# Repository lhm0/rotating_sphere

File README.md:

# Rotating LED Sphere – RP2040 POV Display
**UPDATE December 24th, 2025**
I have made a change to the header of the motor in order to make the connection to the sphere stronger and long term stable.

However, alignment of the rotor now is done by placing washers between header and pcb, if necessary.

Furthermore, I have added a file "print_instructions.pdf" in the /mechanics subfolder, with slicer images of the parts that need nut inlays.

**UPDATE August 29th, 2025**
There are two push switches on the power supply pcb, that control the speed of the motor. The "speed" button is used to increase the motor speed step by step. Once the maximum speed is reached, it jumps back to zero. The "off" button turns the motor off.

However, The buttons were previously positioned at the same height as the power supply circuit board, very close to the rotating sphere assembly. To reduce the risk of injury, I have moved the buttons to the center of the power supply housing in the latest version of the housing. The movement of the two buttons is transferred to the switches on the circuit board purely mechanically, so that no modification of the circuit board is necessary.

**UPDATE May 29th, 2025**

In the meantime I had the new power supply board built and could test it the last couple of days. **It works fine as expected.** 

Power is now supplied from a **standard USB-C power supply** with power delivery ("PD") function via an off-the-shelf USB-C cable. I am using the Apple power supply of my MacBook. The CH224k for controlling the voltage setting works extremely well. The voltage can be set with a 3 bit dip switch, easily. When set to 15 V, the transmitted energy to the LED board is sufficient even for the highest brightness setting. Of course, the losses of the wireless power transmission show up as heat, but the temperature looks reasonable to me.

The motor power supply has a **stronger step-down converter chip** now (TPS54302 instead of TPS54202 in the old design). The circuit allows for up to 3A of motor current. Furthermore, I introduced a button control logic for setting the motor speed in 5 steps. There are two buttons: increase speed, and OFF. This eliminates the potentiometer and the on/off switch in the old design.

Finally, I **increased the diameter of the circular hole in the middle of the pcb**, which allows for a significantly larger and stronger motor to LED-board connection. The tray disk has a larger diameter now. The 4 holes in the secondary coil pcb are now being used for securing the LED assembly to the motor.

In order to fit the new pcb, I had to modify the housing. Please find the related files in this repository.

**UPDATE May 10th, 2025**
I am currently working on an update of the power supply. The idea is to replace the 12V power plug with an USB-C PD (power delivery) power supply. I am interested in the CH224K, which manages the voltage negotiation with the USB PD. This would allow us to use a standard USB-C charger (probably about 25 - 35 W) for supplying the device. USB power delivery can provide 5, 9, 12, 15, or 20V. This is exactly the range needed for the rotating sphere. At the same time I will replace the motor power regulator with a stronger one. Currently, the motor current cannot go above 2A, which is just barely sufficient.

If you are interested, stay tuned. However, it will definitely take 4 weeks, probably more, to get it done.

**UPDATE April 30th, 2025**
@randybeever5206 made me aware (**thank you!**), that the value of R403, R404, and R405 on the main display board should be 270 Ohm according to the schematic, but the properties field and the corresponding line in the production file refers to a 1k resistor instead. Let me explain:

1. these three resistors set the forward peak current of the LEDs. 1k corresponds to 20 mA, 270 Ohms corresponds to 75 mA. 
2. I had copied this part of the schematic from an earlier project, changed the value but missed to change the component in the production data. As a result, I worked with 20mA, although I thought it was 75.
3. I have changed the resistors in my unit from 1k to 270 Ohm in the meantime (what a pain: these are 0402 resistors!). Yes, it is significantly brighter. For some reason, colors look even more saturated, now. The color animation, which can be seen in the video, looks stunning.
4. However, higher brightness means higher power consumption. If you supply the device with a 12 V power plug (12V, 2A), you can not run it at 100% brightness. I found that the processor crashes, when you go too high. This is obviously a voltage breakdown.
5. Fortunately, I designed the power supply such that it can be operated with up to 24V. When you run the sphere with 17V or above, you can go up to 100% brightness.
6. Here is my recommendation: use 270 Ohm resistors. If you run the device at 12V, you need to reduce the brightness setting, so that the device works flawlessly. If you want more, you need a power supply with more than 17V, 2 or better 3 A (consumption depends on motor speed).
7. I have updated the schematic and the production file in the meantime.

## 📌 Project Overview

This project describes the design and construction of a **rotating LED sphere** using the **persistence-of-vision (POV)** principle.  
The device is controlled by a **Raspberry Pi RP2040 microcontroller** and is capable of displaying **videos, animated GIFs**, and **static images** on a spherical 3D surface.

The project is inspired by the Las Vegas Sphere – scaled down to desktop size, but packed with smart engineering like **wireless power transmission**, **real-time SDIO video streaming**, and **web-based remote control**.

All hardware, software, PCB layouts and 3D printable parts are **open source** and included in this repository.

---

## ✨ Features

- 🟡 64 RGB LEDs arranged to form a 170 mm spherical POV display  
- 📊 Display resolution: **64 × 256 pixels** **(corrected: it is NOT 128 x 256)**  
- 🎞️ Supports **.rs64** video/image format (GIFs, animations, stills)  
- 💾 Real-time video streaming from **SD card via SDIO (4-bit)**  
- ⚙️ Driven by an **RP2040** using fast **PIO-based multiplexing**  
- 🌐 Optional **ESP01s** module creates a web-based control interface  
- 🔌 **Wireless power** using a Royer converter – no slip rings needed  
- 🧠 Designed to be **easy to build**, with a minimal part count  
- 🧰 All files included: **KiCad PCB**, **PlatformIO code**, **3D models**

---

## 🧱 System Components

- **RP2040 microcontroller** (via Raspberry Pi Pico or custom PCB)  
- **ESP01s (optional)** for Wi-Fi control and web interface  
- **SD card slot** (with high-speed SDIO interface)  
- **24-bit shift register** and **MOSFETs** for LED driving  
- **3D-printed mechanical components** (rotor, housing, mounts)  
- **Wireless power transmission** with printed transmitter/receiver coils  
- **Hall sensor** for rotation angle synchronization  
- **Custom `.rs64` video format** with 8 brightness levels via PWM

---

## 🛠️ How to Build

The build process is documented in a [step-by-step video tutorial](https://www.youtube.com/yourvideolink), covering:

1. Mechanical design & 3D printing  
2. Rotor balancing and alignment  
3. Soldering the LED matrix  
4. Power & wireless energy transmission  
5. Programming the RP2040 and ESP01s  
6. Creating `.rs64` files from GIFs and videos  
7. Using the web interface

For detailed instructions, see the [`docs/`](./docs) folder.

---

## 📜 License

This project is licensed under the **Creative Commons BY-NC-SA 4.0** license.  
You are free to **use, adapt, and share** this work for **non-commercial** purposes,  
as long as you give proper credit and share your work under the same terms.

> ✏️ Especially welcomed: use in education, maker communities, and open-source development!

---

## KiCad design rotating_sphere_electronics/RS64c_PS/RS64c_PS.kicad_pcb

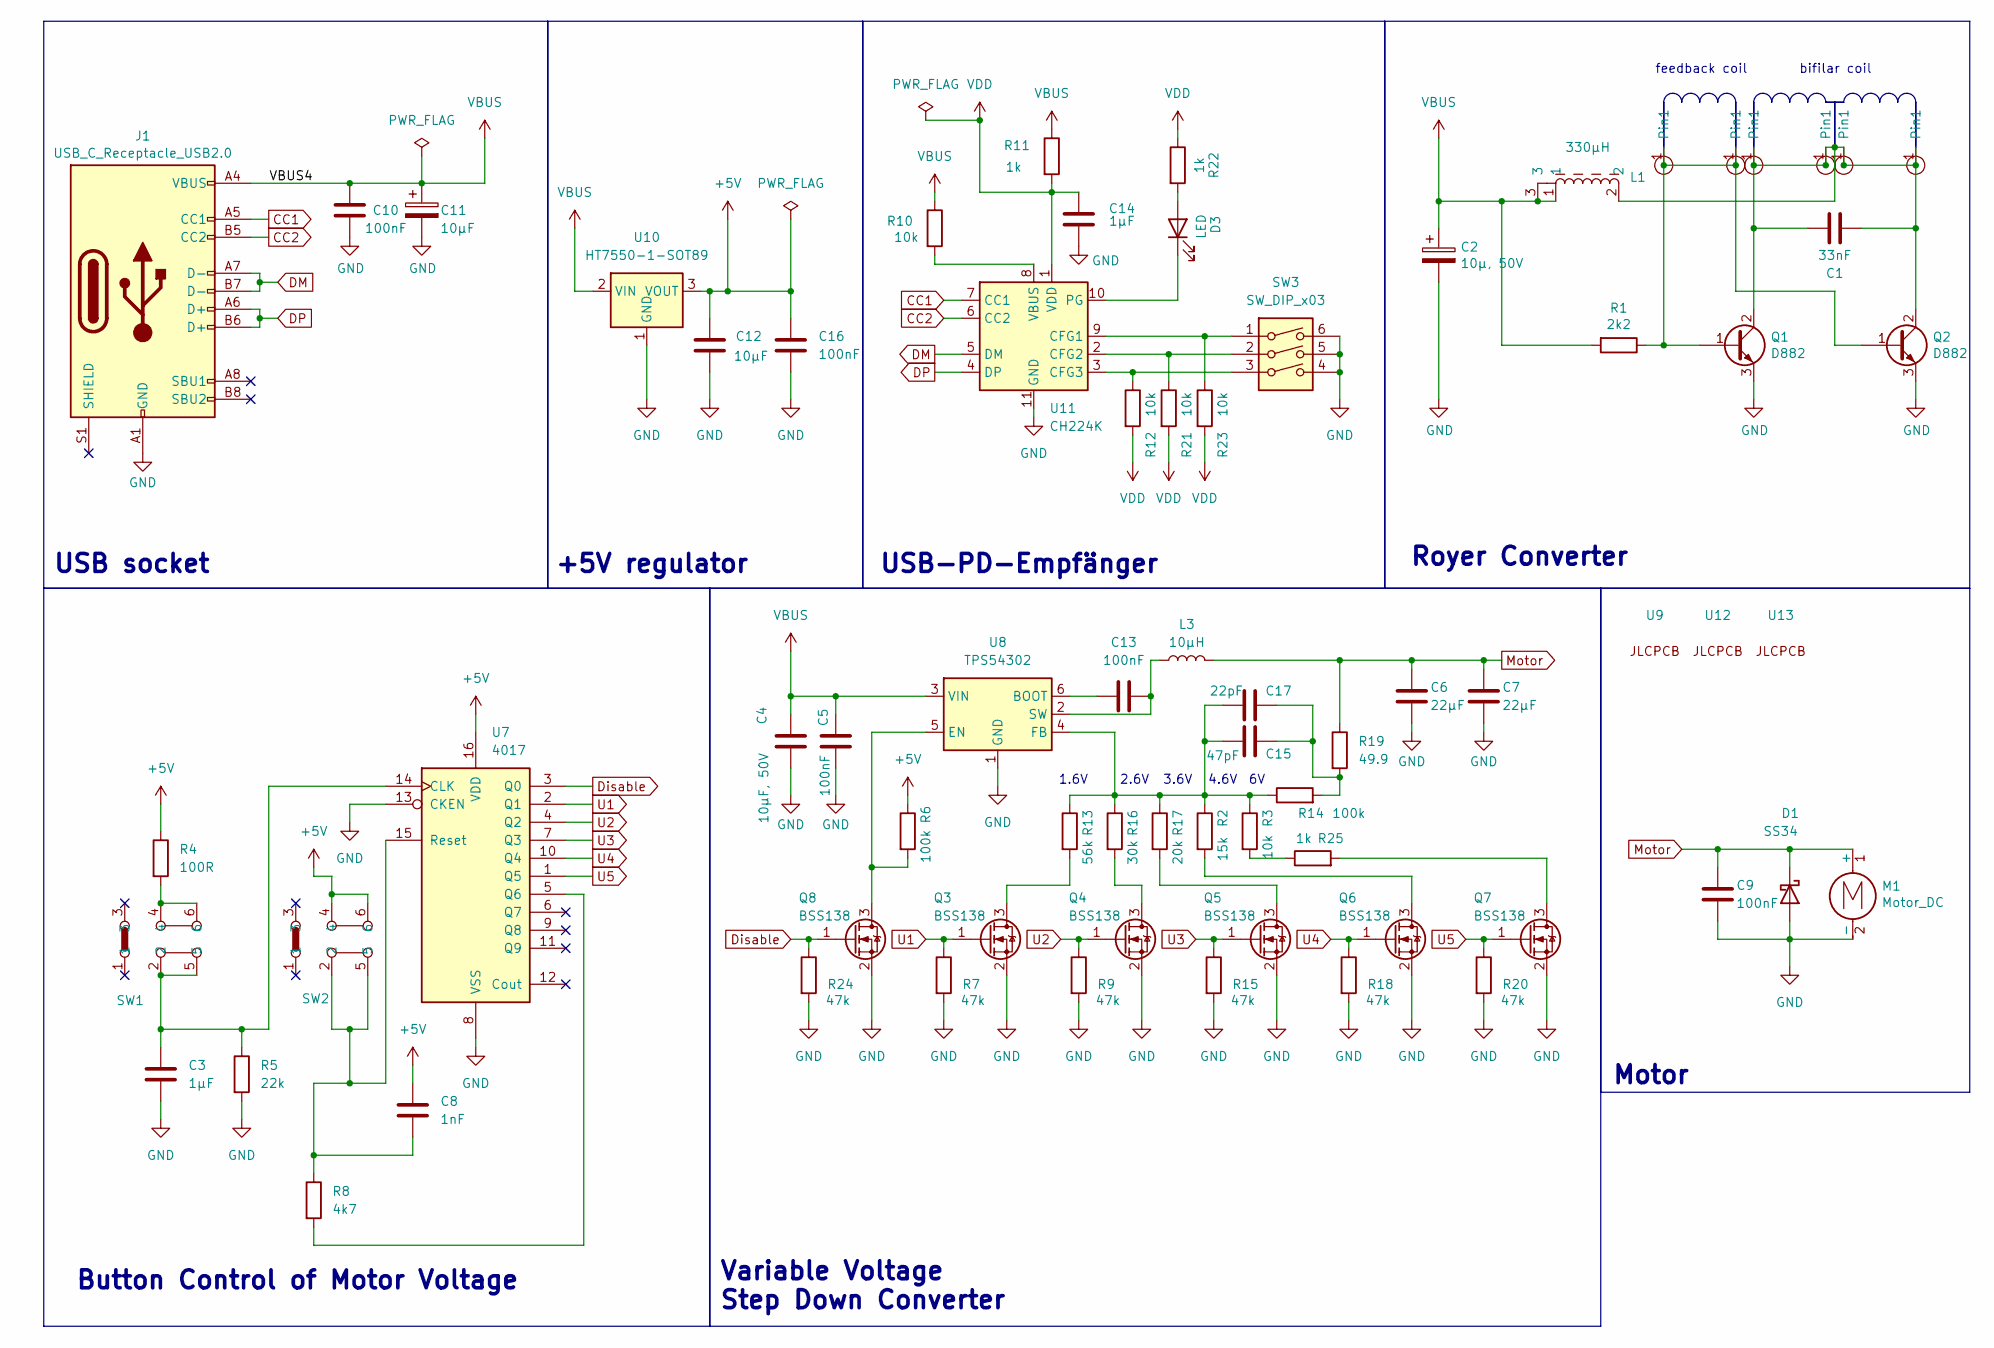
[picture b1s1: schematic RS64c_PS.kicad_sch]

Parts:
C1: 33nF; C_1812_4532Metric; LCSC C97977
C2: 10µ, 50V; C_1206_3216Metric; LCSC C13585
C3, C14: 1µF; C_0603_1608Metric; LCSC C15849
C4: 10µF, 50V; C_1206_3216Metric; LCSC C13585
C5, C9, C13, C16: 100nF; C_0603_1608Metric; LCSC C14663
C6, C7: 22µF; C_0805_2012Metric; LCSC C45783
C8: 1nF; C_0402_1005Metric; LCSC C1523
C10: 100nF; C_0402_1005Metric; LCSC C307331
C11: 10µF; C_0805_2012Metric; LCSC C440198
C12: 10µF; C_1206_3216Metric; LCSC C13585
C15: 47pF; C_0603_1608Metric; LCSC C1671
C17: 22pF; C_0603_1608Metric; LCSC C1653
D1: SS34; DIOM7959X265N; LCSC C8678
D3: LED; LED_0805_2012Metric; LCSC C84256
J1: USB_C_Receptacle_USB2.0; USB_C_Receptacle; LCSC C709357
L1: 330µH; L_SXN_SMDRI127; LCSC C10152
L3: 10µH; L_Bourns_SRP7028A_7.3x6.6mm; LCSC C5189958
M1: Motor_DC; motor
Q1, Q2: D882; LCSC C9634
Q3, Q4, Q5, Q6, Q7, Q8: BSS138; SOT-23; LCSC C7420339
R1: 2k2; R_0603_1608Metric; LCSC C4190
R2: 15k; R_0402_1005Metric; LCSC C25756
R3, R10, R12, R21, R23: 10k; R_0402_1005Metric; LCSC C25744
R4: 100R; R_0402_1005Metric; LCSC C25076
R5: 22k; R_0402_1005Metric; LCSC C25768
R6, R14: 100k; R_0402_1005Metric; LCSC C25741
R7, R9, R15, R18, R20, R24: 47k; R_0402_1005Metric; LCSC C25792
R8: 4k7; R_0402_1005Metric; LCSC C25900
R11, R25: 1k; R_0402_1005Metric; LCSC C11702
R13: 56k; R_0603_1608Metric; LCSC C23206
R16: 30k; R_0603_1608Metric; LCSC C22984
R17: 20k; R_0402_1005Metric; LCSC C25765
R19: 49.9; R_0402_1005Metric; LCSC C25120
R22: 1k; R_0603_1608Metric; LCSC C21190
SW1, SW2: XKB5858-X-F-75; LCSC C780037
SW3: SW_DIP_x03; SW_DIP_SPSTx03_Slide_9.78x9.8mm_W8.61mm_P2.54mm; LCSC C7421520
U1, U2, U3, U4, U5, U6: Pin-Connector; Pin_2mm
U7: 4017; SOP-16_3.9x9.9mm_P1.27mm; LCSC C22390236
U8: TPS54302; SOT-23-6; LCSC C311983
U9, U12, U13: JLC_tooling_hole
U10: HT7550-1-SOT89; SOT-89-3; LCSC C16106
U11: CH224K; SSOP-10-1EP_3.9x4.9mm_P1mm_EP2.1x3.3mm; LCSC C970725

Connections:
+5V: C8.1, C12.1, C16.1, R4.1, R6.1, SW2.4, SW2.6, U7.16 (VDD), U10.3 (VOUT)
CC1: J1.A5 (CC1), U11.7 (CC1)
CC2: J1.B5 (CC2), U11.6 (CC2)
DM: J1.A7 (D-), J1.B7 (D-), U11.5 (DM)
DP: J1.A6 (D+), J1.B6 (D+), U11.4 (DP)
Disable: Q8.1 (G), R24.1, U7.3 (Q0)
GND: C2.2, C3.2, C4.2, C5.2, C6.2, C7.2, C9.2, C10.1, C11.2, C12.2, C14.2, C16.2, D1.2 (A), J1.A1 (GND), J1.A12 (GND), J1.B1 (GND), J1.B12 (GND), M1.2 (-), Q1.3 (E), Q2.3 (E), Q3.2 (S), Q4.2 (S), Q5.2 (S), Q6.2 (S), Q7.2 (S), Q8.2 (S), R5.2, R7.2, R9.2, R15.2, R18.2, R20.2, R24.2, SW3.4, SW3.5, SW3.6, U7.8 (VSS), U7.13 (CKEN), U8.1 (GND), U10.1 (GND), U11.11 (GND)
Motor: C6.1, C7.1, C9.1, D1.1 (K), L3.2, M1.1 (+), R19.1
unnamed: C15.2, C17.2, R14.2, R19.2
unnamed: D3.2 (A), R22.2
unnamed: D3.1 (K), U11.10 (PG)
unnamed: Q1.1 (B), Q2.1 (B), R1.1, U1.1 (Pin1), U2.1 (Pin1)
unnamed: C1.1, C1.2, L1.2, Q1.2 (C), Q2.2 (C), U3.1 (Pin1), U4.1 (Pin1), U5.1 (Pin1), U6.1 (Pin1)
unnamed: Q3.3 (D), R13.2
unnamed: Q4.3 (D), R16.2
unnamed: Q5.3 (D), R17.2
unnamed: Q6.3 (D), R2.2
unnamed: Q7.3 (D), R25.2
unnamed: Q8.3 (D), R6.2, U8.5 (EN)
unnamed: R4.2, SW1.4, SW1.6
unnamed: R3.2, R25.1
unnamed: C3.1, R5.1, SW1.2, SW1.5, U7.14 (CLK)
unnamed: R8.2, U7.5 (Q6)
unnamed: C8.2, R8.1, SW2.2, SW2.5, U7.15 (Reset)
unnamed: C13.1, U8.6 (BOOT)
unnamed: C15.1, C17.1, R2.1, R3.1, R13.1, R14.1, R16.1, R17.1, U8.4 (FB)
unnamed: C13.2, L3.1, U8.2 (SW)
unnamed: R23.1, SW3.1, U11.9 (CFG1)
unnamed: R21.1, SW3.2, U11.2 (CFG2)
unnamed: R12.1, SW3.3, U11.3 (CFG3)
unnamed: R10.2, U11.8 (VBUS)
U1: Q3.1 (G), R7.1, U7.2 (Q1)
U2: Q4.1 (G), R9.1, U7.4 (Q2)
U3: Q5.1 (G), R15.1, U7.7 (Q3)
U4: Q6.1 (G), R18.1, U7.10 (Q4)
U5: Q7.1 (G), R20.1, U7.1 (Q5)
VBUS: C2.1, C4.1, C5.1, C10.2, C11.1, J1.A4 (VBUS), J1.A9 (VBUS), J1.B4 (VBUS), J1.B9 (VBUS), L1.1, L1.3, R1.2, R10.1, R11.1, U8.3 (VIN), U10.2 (VIN)
VDD: C14.1, R11.2, R12.2, R21.2, R22.1, R23.2, U11.1 (VDD)

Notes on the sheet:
+5V regulator
3.6V
Motor
Royer Converter
feedback coil
4.6V
USB-PD-Empfänger
Variable Voltage Step Down Converter
USB socket
1.6V
bifilar coil
2.6V
Button Control of Motor Voltage

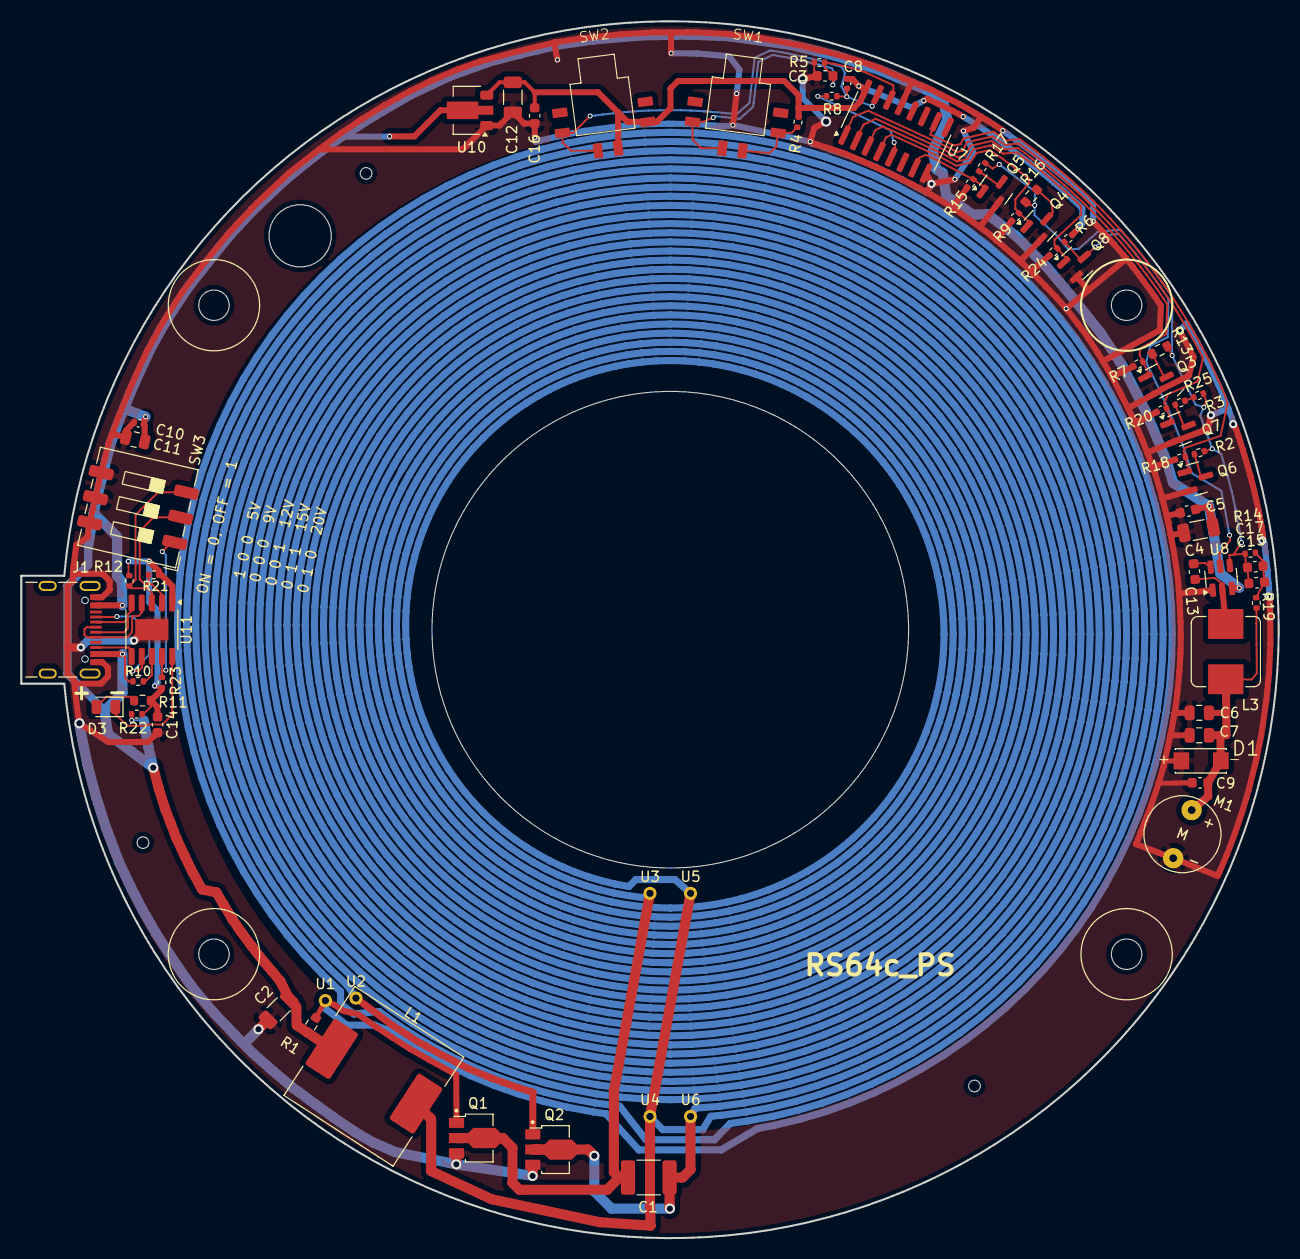
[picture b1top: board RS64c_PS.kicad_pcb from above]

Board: 2 copper layers, 124.0 x 120.0 mm, 72 parts (0 on the bottom side), 38 nets.

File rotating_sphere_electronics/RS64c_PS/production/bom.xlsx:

Designator | Footprint | Quantity | Value | LCSC Part #
C1 | 1812 | 1 | 33nF | C97977
C10 | 0402 | 1 | 100nF | C307331
C11 | 0805 | 1 | 10µF | C440198
C12 | 1206 | 1 | 10µF | C13585
C13, C16, C5, C9 | 0603 | 4 | 100nF | C14663
C14, C3 | 0603 | 2 | 1µF | C15849
C15 | 0603 | 1 | 47pF | C1671
C17 | 0603 | 1 | 22pF | C1653
C2 | 1206 | 1 | 10µ, 50V | C13585
C4 | 1206 | 1 | 10µF, 50V | C13585
C6, C7 | 0805 | 2 | 22µF | C45783
C8 | 0402 | 1 | 1nF | C1523
D1 | DIOM7959X265N | 1 | SS34 | C8678
D3 | 0805 | 1 | LED | C84256
J1 | USB_C_Receptacle | 1 | USB_C_Receptacle_USB2.0 | C709357
L1 | L_SXN_SMDRI127 | 1 | 330µH | C10152
L3 | L_Bourns_SRP7028A_7.3x6.6mm | 1 | 10µH | C5189958
Q1, Q2 | D882 | 2 | D882 | C9634
Q3, Q4, Q5, Q6, Q7, Q8 | SOT-23 | 6 | BSS138 | C7420339
R1 | 0603 | 1 | 2k2 | C4190
R10, R12, R21, R23, R3 | 0402 | 5 | 10k | C25744
R11, R25 | 0402 | 2 | 1k | C11702
R13 | 0603 | 1 | 56k | C23206
R14, R6 | 0402 | 2 | 100k | C25741
R15, R18, R20, R24, R7, R9 | 0402 | 6 | 47k | C25792
R16 | 0603 | 1 | 30k | C22984
R17 | 0402 | 1 | 20k | C25765
R19 | 0402 | 1 | 49.9 | C25120
R2 | 0402 | 1 | 15k | C25756
R22 | 0603 | 1 | 1k | C21190
R4 | 0402 | 1 | 100R | C25076
R5 | 0402 | 1 | 22k | C25768
R8 | 0402 | 1 | 4k7 | C25900
SW1, SW2 | XKB5858-X-F-75 | 2 | ~ | C780037
SW3 | SW_DIP_SPSTx03_Slide_9.78x9.8mm_W8.61mm_P2.54mm | 1 | SW_DIP_x03 | C7421520
U10 | SOT-89-3 | 1 | HT7550-1-SOT89 | C16106
U11 | SSOP-10-1EP_3.9x4.9mm_P1mm_EP2.1x3.3mm | 1 | CH224K | C970725
U7 | SOP-16_3.9x9.9mm_P1.27mm | 1 | 4017 | C22390236
U8 | SOT-23-6 | 1 | TPS54302 | C311983

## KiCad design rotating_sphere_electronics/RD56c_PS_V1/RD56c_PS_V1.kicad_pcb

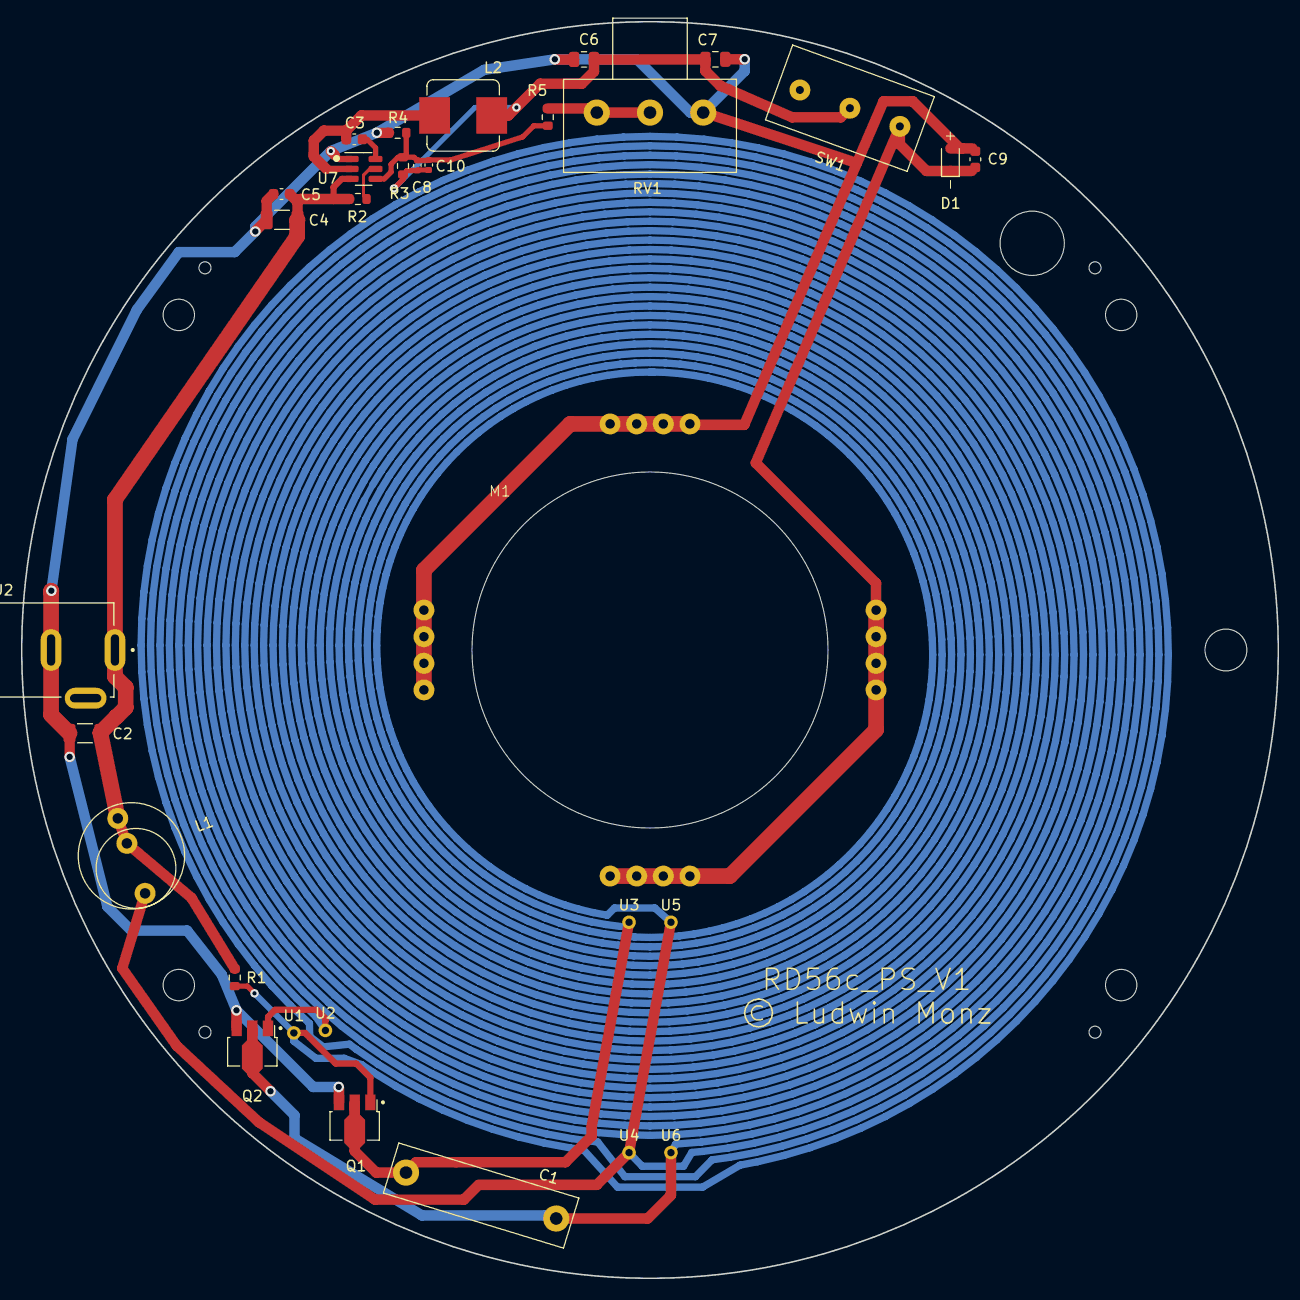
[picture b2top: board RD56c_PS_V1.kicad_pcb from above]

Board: 2 copper layers, 120.0 x 120.0 mm, 31 parts (0 on the bottom side), 11 nets.

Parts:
C1: 33nF; MKP10_630V
C2: 10µ, 50V; C_1206_3216Metric
C3, C5, C9: 100nF; C_0603_1608Metric
C4: 10µF, 50V; C_1206_3216Metric
C6, C7: 22µF, 25V; C_0805_2012Metric
C8: 47pF; C_0402_1005Metric
C10: 10pF; C_0402_1005Metric
D1: 1N5819
J2: Barrel_Jack_Switch_Pin3Ring; GRAVITECH_CON-SOCJ-2155
L1: 330µH; L_vertical12
L2: 33µH; L_Bourns_SRP7028A_7.3x6.6mm
M1: Motor_DC; motor_tray
Q1, Q2: D882
R1: 2k2; R_0603_1608Metric
R2, R3: 100k; R_0603_1608Metric
R4: 120k; R_0603_1608Metric
R5: 12k; R_0603_1608Metric
RV1: 100k; Poti_10mm
SW1: SW_DPDT_x2; Switch1
U1, U2, U3, U4, U5, U6: Pin-Connector; Pin_2mm
U7: TPS54202DDC; SOT-23-6

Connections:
+12V: C2.1, C4.1, C5.1, J2.1, L1.1, L1.3, R1.2, R2.1, U7.3 (VIN)
GND: C2.2, C4.2, C5.2, C6.2, C7.2, C9.2, D1.2 (A), J2.3, M1.2 (-), Q1.3 (E), Q2.3 (E), R4.2, RV1.1, U7.1 (GND)
unnamed: C9.1, D1.1 (K), M1.1 (+), SW1.3 (C)
unnamed: Q1.1 (B), Q2.1 (B), R1.1, U1.1 (Pin1), U2.1 (Pin1)
unnamed: C1.1, C1.2, L1.2, Q1.2 (C), Q2.2 (C), U3.1 (Pin1), U4.1 (Pin1), U5.1 (Pin1), U6.1 (Pin1)
unnamed: R5.2, RV1.2, RV1.3
unnamed: C6.1, C7.1, C8.1, C10.1, L2.2, R3.2, SW1.2 (B)
unnamed: C3.1, U7.6 (BOOT)
unnamed: R2.2, U7.5 (EN)
unnamed: C8.2, C10.2, R3.1, R4.1, R5.1, U7.4 (FB)
unnamed: C3.2, L2.1, U7.2 (SW)

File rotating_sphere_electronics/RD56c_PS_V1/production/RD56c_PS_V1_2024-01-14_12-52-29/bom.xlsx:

Designator | Footprint | Quantity | Value | LCSC Part #
C10 | 0402 | 1 | 10pF | C32949
C2 | 1206 | 1 | 10µ, 50V | C13585
C3, C5, C9 | 0603 | 3 | 100nF | C14663
C4 | 1206 | 1 | 10µF, 50V | C13585
C6, C7 | 0805 | 2 | 22µF, 25V | C45783
C8 | 0402 | 1 | 47pF | C1567
D1 | 1N5819 | 1 | 1N5819 | C191023
L2 | L_Bourns_SRP7028A_7.3x6.6mm | 1 | 33µH | C177245
Q1, Q2 | D882 | 2 | D882 | C9634
R1 | 0603 | 1 | 2k2 | C4190
R2, R3 | 0603 | 2 | 100k | C25803
R4 | 0603 | 1 | 120k | C25808
R5 | 0603 | 1 | 12k | C22790
U7 | SOT-23-6 | 1 | TPS54202DDC | C191884

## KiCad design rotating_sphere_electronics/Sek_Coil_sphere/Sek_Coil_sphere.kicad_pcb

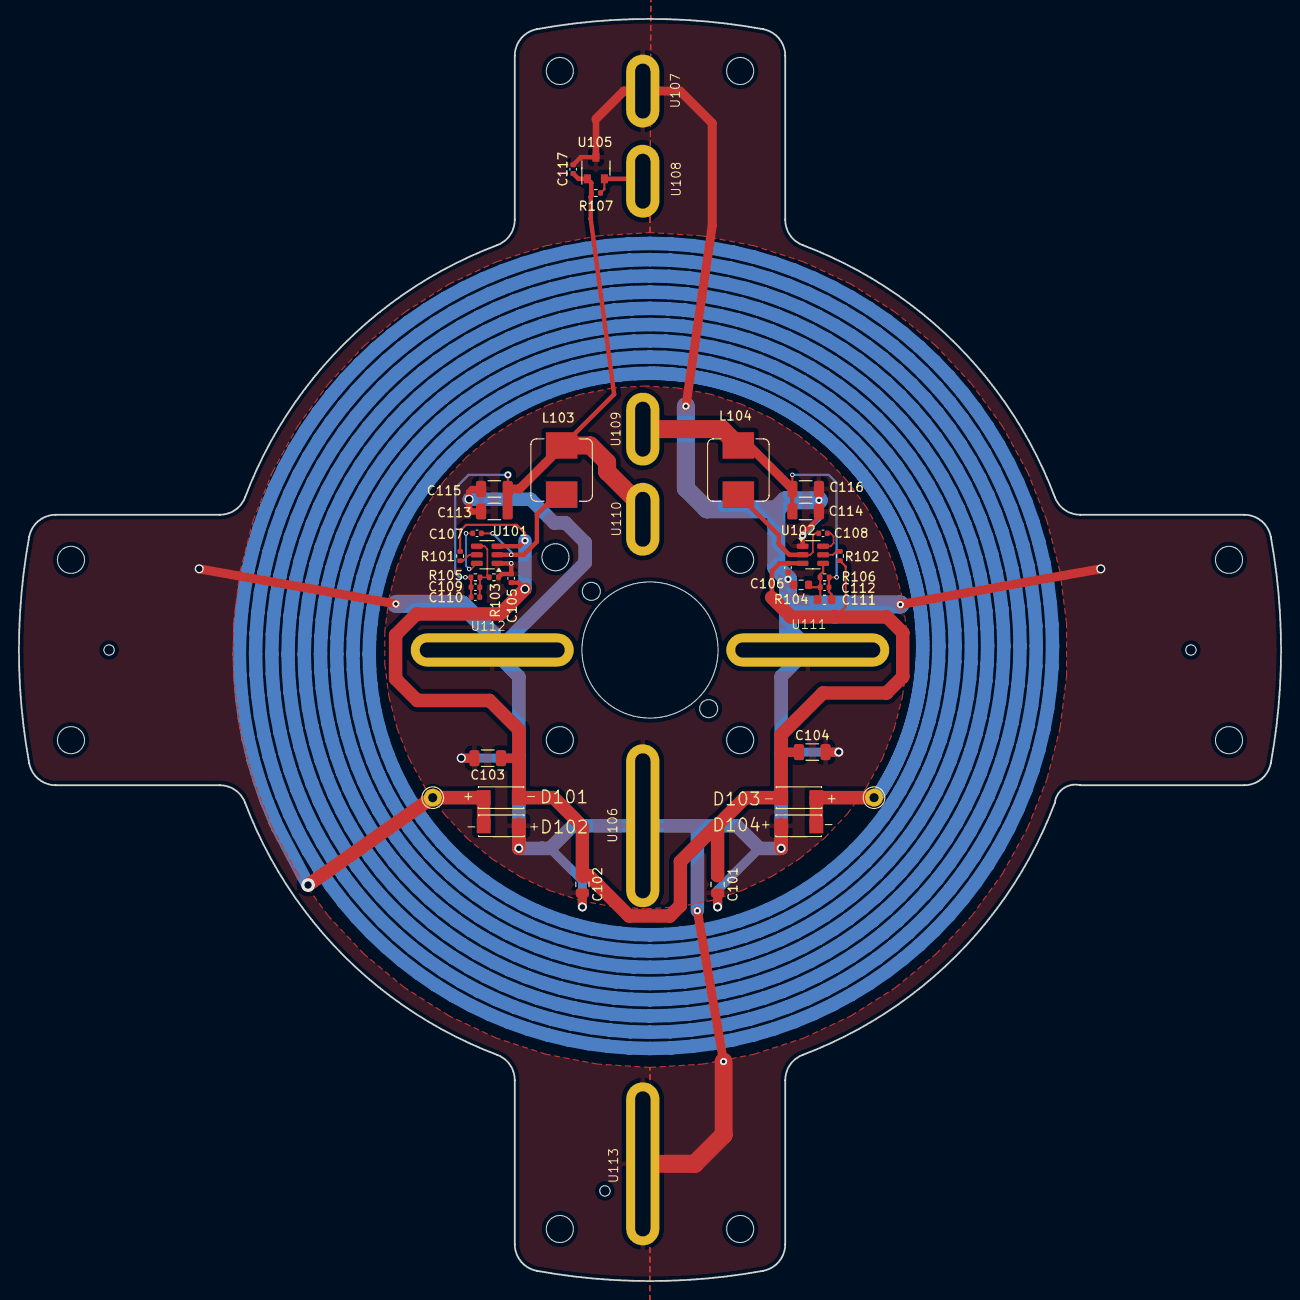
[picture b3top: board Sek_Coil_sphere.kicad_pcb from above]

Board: 2 copper layers, 140.0 x 140.0 mm, 43 parts (0 on the bottom side), 14 nets.

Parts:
C101, C102: 22µF, 25V; C_0805_2012Metric
C103, C104: 10µF, 50V; C_1206_3216Metric
C105, C106, C107, C108, C117: 100nF; C_0402_1005Metric
C109, C112: 47pF; C_0402_1005Metric
C110: 10pF; C_0402_1005Metric
C111: 30pF; C_0603_1608Metric
C113, C114, C115, C116: 22µF, 25V; C_1206_3216Metric
D101, D102, D103, D104: SS34; DIOM7959X265N
L103, L104: 33µH; L_Bourns_SRP7028A_7.3x6.6mm
R101, R102, R105, R106: 100k; R_0402_1005Metric
R103: 22k; R_0402_1005Metric
R104: 13k; R_0603_1608Metric
R107: 20k; R_0402_1005Metric
U101, U102: TPS54202DDC; SOT-23-6
U103, U104: Pin_D1.0mm
U105: MH253
U106, U111, U112, U113: slot_long
U107, U108, U109, U110: slot_short

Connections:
+3.3V: C109.1, C110.1, C113.1, C115.1, C117.1, L103.2, R105.2, R107.1, U105.1 (Vcc), U110.1
+5V: C111.1, C112.1, C114.1, C116.1, L104.2, R106.2, U109.1
/EN_BC1: R101.2, U101.5 (EN)
/EN_BC2: R102.2, U102.5 (EN)
/FB_BC1: C109.2, C110.2, R103.2, R105.1, U101.4 (FB)
/FB_BC2: C111.2, C112.2, R104.2, R106.1, U102.4 (FB)
/SW_BC1: C107.2, L103.1, U101.2 (SW)
/SW_BC2: C108.2, L104.1, U102.2 (SW)
/U_unreg: C101.1, C102.1, C103.1, C104.1, C105.1, C106.1, D101.1 (K), D103.1 (K), R101.1, R102.1, U101.3 (VIN), U102.3 (VIN)
/boot_BC1: C107.1, U101.6 (BOOT)
/boot_BC2: C108.1, U102.6 (BOOT)
/coil1: D101.2 (A), D102.1 (K), D103.2 (A), D104.1 (K), U103.1 (pin), U104.1 (pin)
GND: C101.2, C102.2, C103.2, C104.2, C105.2, C106.2, C113.2, C114.2, C115.2, C116.2, C117.2, D102.2 (A), D104.2 (A), R103.1, R104.1, U101.1 (GND), U102.1 (GND), U105.3 (Ground), U106.1, U107.1, U111.1, U112.1, U113.1
unnamed: R107.2, U105.2 (Output), U108.1

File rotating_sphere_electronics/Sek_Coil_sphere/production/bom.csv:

Designator;Footprint;Quantity;Value;LCSC Part #
C101, C102;0805;2;22µF, 25V;C45783
C103, C104;1206;2;10µF, 50V;C13585
C105, C106, C107, C108, C117;0402;5;100nF;C307331
C109, C112;0402;2;47pF;C1567
C110;0402;1;10pF;C32949
C111;0603;1;30pF;C1658
C113, C114, C115, C116;1206;4;22µF, 25V;C12891
D101, D102, D103, D104;DIOM7959X265N;4;SS34;C8678
L103, L104;L_Bourns_SRP7028A_7.3x6.6mm;2;33µH;C177245
R101, R102, R105, R106;0402;4;100k;C25741
R103;0402;1;22k;C25768
R104;0603;1;13k;C22797
R107;0402;1;20k;C25765
U101, U102;SOT-23-6;2;TPS54202DDC;C191884
U105;MH253;1;MH253;C114369

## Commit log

2025-04-18 BOM added
2025-04-28 deleted bom.csv and positions.csv in the production files
2025-04-28 how to order PCBs from JLCPCB
2025-04-30 R403, 404, 405 corrected
2025-04-30 more testing results in readme.md on the 270 Ohm brightness resistors
2025-05-04 display layout complete
2025-05-04 BOM updated
2025-05-14 new PS design complete
2025-05-29 new PS design released, readme.md updated
2025-08-29 update of readme, new stl files for power supply base
2025-09-16 Remove tracked .DS_Store files and ignore them
2025-12-24 print instructions added. readme.md updated
2026-02-09 added some photos

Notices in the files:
rotating_sphere_electronics/RD56c_PS_V1/RD56c_PS_V1.kicad_pcb:
© Ludwin Monz
rotating_sphere_electronics/RS64c_PS/RS64c_PS.kicad_sch:
https://creativecommons.org/licenses/by-nc-sa/4.0
License: Creative Commons Attribution-Non-Commercial (CC BY-NC-SA)
